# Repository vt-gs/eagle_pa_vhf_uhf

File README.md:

# eagle_pa_vhf_uhf
VHF/UHF Power Amplifier control board EagleCAD files

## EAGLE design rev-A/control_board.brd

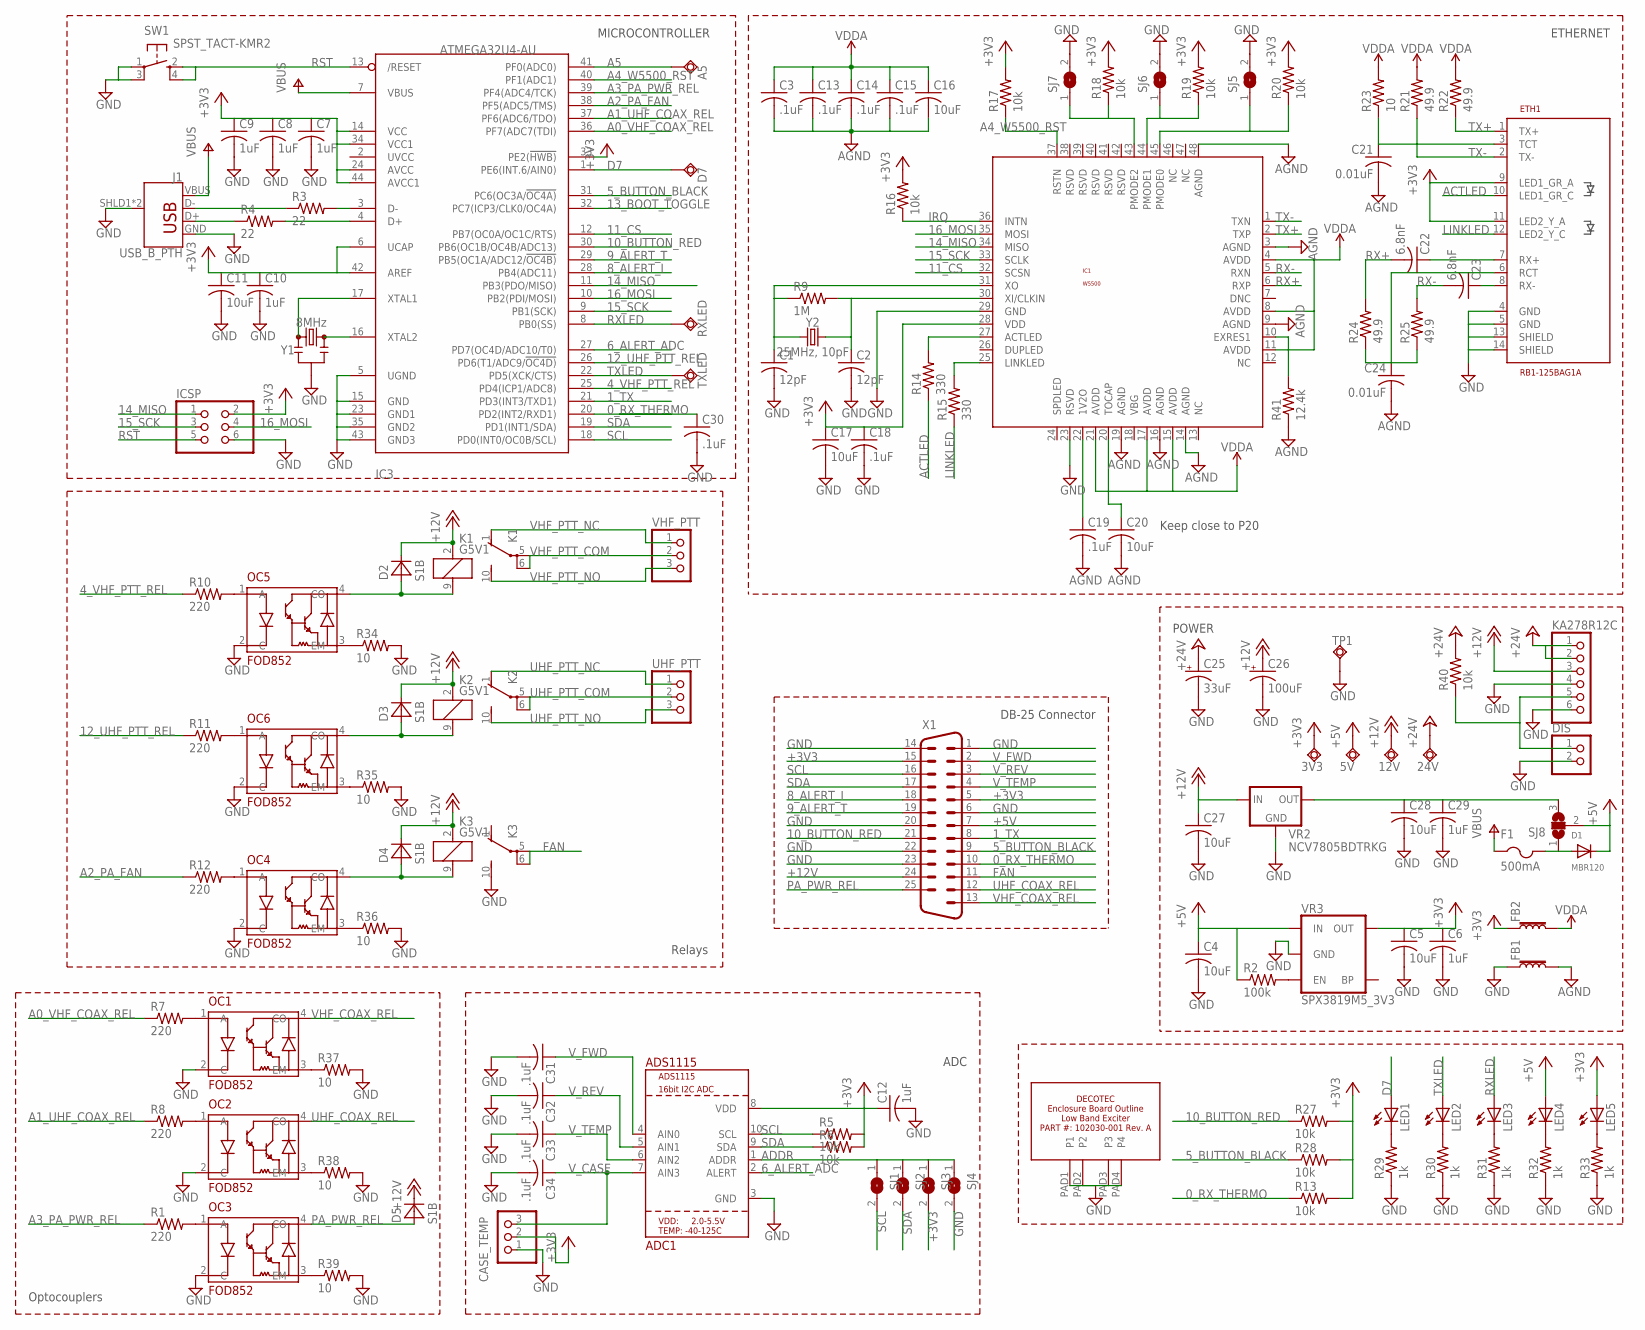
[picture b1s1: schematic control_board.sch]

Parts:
3V3, 5V, 12V, 24V: TPSQTP20SQ; TP20SQ
A5: TPSQTP20SQ; TP20SQ
ADC1: ADS1115; MSOP10
C1, C2: 12pF; C0805K
C3, C13, C14, C15, C18, C19, C30, C31, C32, C33, C34: .1uF; C0805K
C4, C5, C11, C16, C17, C20, C27, C28: 10uF; C0805K
C6, C7, C8, C9, C10, C12, C29: 1uF; C0805K
C21, C24: 0.01uF; C0805K
C22, C23: 6.8nF; C0805K
C25: 33uF; PANASONIC_C
C26: 100uF; PANASONIC_D
CASE_TEMP: PINHD-1X3; 1X03
D1: MBR120; SOD-123
D2, D3, D4, D5: S1B; DO214AC
D7: TPSQTP20SQ; TP20SQ
DIS: PINHD-1X2; 1X02
ETH1: RB1-125BAG1A
F1: 500mA; R1206
FB1, FB2: FERRITE_BEAD; 0805
IC1: W5500; LQFP48
IC3: ATMEGA32U4-AU; TQFP44
ICSP: PINHD-2X3; 2X03
J1: USB_B_PTH; USB-B-PTH
K1, K2, K3: G5V1
KA278R12C: PINHD-1X6; 1X06
LED1, LED2, LED3, LED4, LED5: LEDCHIPLED_0805; CHIPLED_0805
OC1, OC2, OC3, OC4, OC5, OC6: FOD852; SMD4-7
R1, R7, R8, R10, R11, R12: 220; R0805
R2: 100k; R0805
R3, R4: 22; R0805
R5, R6, R13, R16, R17, R18, R19, R20, R27, R28, R40: 10k; R0805
R9: 1M; R0805
R14, R15: 330; R0805
R21, R22, R24, R25: 49.9; R0805
R23, R34, R35, R36, R37, R38, R39: 10; R0805
R29, R30, R31, R32, R33: 1k; R0805
R41: 12.4k; R0805
RXLED: TPSQTP20SQ; TP20SQ
SJ1, SJ2, SJ3, SJ4, SJ5, SJ6, SJ7: SJ
SJ8: SJ2W; SJ_2
SW1: SPST_TACT-KMR2; KMR2
TP1: TPSQTP20SQ; TP20SQ
TXLED: TPSQTP20SQ; TP20SQ
U$3: DECOTEC_102030-001AV3; DECOTEC_102030-001A_V3
UHF_PTT: PINHD-1X3; 1X03
VHF_PTT: PINHD-1X3; 1X03
VR2: NCV7805BDTRKG; DPACK
VR3: SPX3819M5_3V3; SOT23-5
X1: DB25_MALEVB; M25VB
Y1: 8MHz; RESONATOR-SMD-3.2X1.3
Y2: 25MHz, 10pF; CRYSTAL-SMD-3.2X2.5MM

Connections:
0_RX_THERMO: C30.1, IC3.20 (PD2(INT2/RXD1)), R13.1, X1.10
1_TX: IC3.21 (PD3(INT3/TXD1)), X1.8
4_VHF_PTT_REL: IC3.25 (PD4(ICP1/ADC8)), R10.1
5_BUTTON_BLACK: IC3.31 (PC6(OC3A/!OC4A)), R28.1, X1.9
6_ALERT_ADC: ADC1.2 (ALERT), IC3.27 (PD7(OC4D/ADC10/T0))
8_ALERT_I: IC3.28 (PB4(ADC11)), X1.18
9_ALERT_T: IC3.29 (PB5(OC1A/ADC12/!OC4B)), X1.19
10_BUTTON_RED: IC3.30 (PB6(OC1B/OC4B/ADC13)), R27.1, X1.21
11_CS: IC1.32 (SCSN), IC3.12 (PB7(OC0A/OC1C/RTS))
12_UHF_PTT_REL: IC3.26 (PD6(T1/ADC9/!OC4D)), R11.1
13_BOOT_TOGGLE: IC3.32 (PC7(ICP3/CLK0/OC4A))
14_MISO: IC1.34 (MISO), IC3.11 (PB3(PDO/MISO)), ICSP.1
15_SCK: IC1.33 (SCLK), IC3.9 (PB1(SCK)), ICSP.3
16_MOSI: IC1.35 (MOSI), IC3.10 (PB2(PDI/MOSI)), ICSP.4
+3V3: 3V3.TP, ADC1.8 (VDD), C5.1, C6.1, C7.1, C8.1, C9.1, C10.1, C11.1, C12.1, C17.1, C18.1, CASE_TEMP.2, ETH1.9 (LED1_GR_A), ETH1.11 (LED2_Y_A), FB2.1, IC1.28 (VDD), IC3.6 (UCAP), IC3.14 (VCC), IC3.24 (AVCC), IC3.33 (PE2(!HWB)), IC3.34 (VCC1), IC3.42 (AREF), IC3.44 (AVCC1), ICSP.2, LED5.A, R5.2, R6.2, R13.2, R16.2, R17.2, R18.2, R19.2, R20.2, R27.2, R28.2, SJ3.2, VR3.5 (OUT), X1.5, X1.15
+5V: 5V.TP, C4.1, D1.C, LED4.A, R2.1, SJ8.2, VR3.1 (IN), X1.7
+12V: 12V.TP, C26.+, C27.1, D2.C, D3.C, D4.C, D5.C, K1.2 (1), K2.2 (1), K3.2 (1), KA278R12C.3, VR2.1 (IN), X1.24
+24V: 24V.TP, C25.+, KA278R12C.1, KA278R12C.2, R40.2
A0_VHF_COAX_REL: IC3.36 (PF7(ADC7(TDI)), R7.1
A1_UHF_COAX_REL: IC3.37 (PF6(ADC6/TDO)), R8.1
A2_PA_FAN: IC3.38 (PF5(ADC5/TMS)), R12.1
A3_PA_PWR_REL: IC3.39 (PF4(ADC4/TCK)), R1.1
A4_W5500_RST: IC1.37 (RSTN), IC3.40 (PF1(ADC1)), R17.1
A5: A5.TP, IC3.41 (PF0(ADC0))
ACTLED: ETH1.10 (LED1_GR_C), R14.1
ADDR: ADC1.1 (ADDR), SJ1.1, SJ2.1, SJ3.1, SJ4.1
AGND: C3.2, C13.2, C14.2, C15.2, C16.2, C19.2, C20.2, C21.2, C24.2, FB1.2, IC1.3 (AGND), IC1.9 (AGND), IC1.14 (AGND), IC1.16 (AGND), IC1.19 (AGND), IC1.48 (AGND), R41.1
D7: D7.TP, IC3.1 (PE6(INT.6/AIN0)), LED1.A
FAN: K3.5, K3.6, X1.11
GND: ADC1.3 (GND), C1.2, C2.2, C4.2, C5.2, C6.2, C7.2, C8.2, C9.2, C10.2, C11.2, C12.2, C17.2, C18.2, C25.-, C26.-, C27.2, C28.2, C29.2, C30.2, C31.2, C32.2, C33.2, C34.2, CASE_TEMP.1, DIS.2, ETH1.4 (GND), ETH1.5 (GND), ETH1.13 (SHIELD), ETH1.14 (SHIELD), FB1.1, IC1.23 (RSVD), IC1.29 (GND), IC3.5 (UGND), IC3.15 (GND), IC3.23 (GND1), IC3.35 (GND2), IC3.43 (GND3), ICSP.6, J1.GND, J1.SHLD1 (SHIELD), J1.SHLD2 (SHIELD), K3.10 (S), KA278R12C.4, KA278R12C.6, OC1.2 (C), OC2.2 (C), OC3.2 (C), OC4.2 (C), OC5.2 (C), OC6.2 (C), R29.1, R30.1, R31.1, R32.1, R33.1, R34.2, R35.2, R36.2, R37.2, R38.2, R39.2, SJ4.2, SJ5.2, SJ6.2, SJ7.2, SW1.1, SW1.3 (P1), TP1.TP, U$3.PAD1 (P1), U$3.PAD2 (P2), U$3.PAD3 (P3), U$3.PAD4 (P4), VR2.4 (GND), VR3.2 (GND), X1.1, X1.6, X1.14, X1.20, X1.22, X1.23, Y1.2
IRQ: IC1.36 (INTN), R16.1
LINKLED: ETH1.12 (LED2_Y_C), R15.1
unnamed: OC3.1 (A), R1.2
unnamed: D4.A, K3.9 (2), OC4.4 (CO)
unnamed: R2.2, VR3.3 (EN)
unnamed: IC3.17 (XTAL1), Y1.1
unnamed: IC3.16 (XTAL2), Y1.3
unnamed: C1.1, IC1.31 (XO), R9.1, Y2.1
unnamed: C2.1, IC1.30 (XI/CLKIN), R9.2, Y2.3 (2)
unnamed: J1.D-, R3.1
unnamed: IC3.3 (D-), R3.2
unnamed: IC3.4 (D+), R4.2
unnamed: J1.D+, R4.1
unnamed: OC1.1 (A), R7.2
unnamed: OC2.1 (A), R8.2
unnamed: OC5.1 (A), R10.2
unnamed: LED1.C, R29.2
unnamed: LED2.C, R30.2
unnamed: LED4.C, R32.2
unnamed: LED5.C, R33.2
unnamed: OC6.1 (A), R11.2
unnamed: OC4.1 (A), R12.2
unnamed: D2.A, K1.9 (2), OC5.4 (CO)
unnamed: D3.A, K2.9 (2), OC6.4 (CO)
unnamed: LED3.C, R31.2
unnamed: OC5.3 (EM), R34.1
unnamed: OC6.3 (EM), R35.1
unnamed: OC4.3 (EM), R36.1
unnamed: OC1.3 (EM), R37.1
unnamed: IC1.27 (ACTLED), R14.2
unnamed: IC1.25 (LINKLED), R15.2
unnamed: C28.1, C29.1, SJ8.3, VR2.3 (OUT)
unnamed: OC2.3 (EM), R38.1
unnamed: C20.1, IC1.20 (TOCAP)
unnamed: C19.1, IC1.22 (1V2O)
unnamed: C23.1, ETH1.8 (RX-)
unnamed: C22.1, ETH1.7 (RX+)
unnamed: C24.1, ETH1.6 (RCT), R24.1, R25.1
unnamed: D1.A, F1.2, SJ8.1
unnamed: OC3.3 (EM), R39.1
unnamed: DIS.1, KA278R12C.5, R40.1
unnamed: IC1.10 (EXRES1), R41.2
PA_PWR_REL: D5.A, OC3.4 (CO), X1.25
PMODE0: IC1.45 (PMODE0), R20.1, SJ5.1
PMODE1: IC1.44 (PMODE1), R19.1, SJ6.1
PMODE2: IC1.43 (PMODE2), R18.1, SJ7.1
RST: IC3.13 (/RESET), ICSP.5, SW1.2 (S), SW1.4 (S1)
RX+: C22.2, IC1.6 (RXP), R24.2
RX-: C23.2, IC1.5 (RXN), R25.2
RXLED: IC3.8 (PB0(SS)), LED3.A, RXLED.TP
SCL: ADC1.10 (SCL), IC3.18 (PD0(INT0/OC0B/SCL)), R5.1, SJ1.2, X1.16
SDA: ADC1.9 (SDA), IC3.19 (PD1(INT1/SDA)), R6.1, SJ2.2, X1.17
TCT: C21.1, ETH1.3 (TCT), R23.1
TX+: ETH1.1 (TX+), IC1.2 (TXP), R22.1
TX-: ETH1.2 (TX-), IC1.1 (TXN), R21.1
TXLED: IC3.22 (PD5(XCK/CTS)), LED2.A, TXLED.TP
UHF_COAX_REL: OC2.4 (CO), X1.12
UHF_PTT_COM: K2.5, K2.6, UHF_PTT.2
UHF_PTT_NC: K2.1 (O), UHF_PTT.1
UHF_PTT_NO: K2.10 (S), UHF_PTT.3
VBUS: F1.1, IC3.7 (VBUS), J1.VBUS
VDDA: C3.1, C13.1, C14.1, C15.1, C16.1, FB2.2, IC1.4 (AVDD), IC1.8 (AVDD), IC1.11 (AVDD), IC1.15 (AVDD), IC1.17 (AVDD), IC1.21 (AVDD), R21.2, R22.2, R23.2
VHF_COAX_REL: OC1.4 (CO), X1.13
VHF_PTT_COM: K1.5, K1.6, VHF_PTT.2
VHF_PTT_NC: K1.1 (O), VHF_PTT.1
VHF_PTT_NO: K1.10 (S), VHF_PTT.3
V_CASE: ADC1.7 (AIN3), C34.1, CASE_TEMP.3
V_FWD: ADC1.4 (AIN0), C31.1, X1.2
V_REV: ADC1.5 (AIN1), C32.1, X1.3
V_TEMP: ADC1.6 (AIN2), C33.1, X1.4

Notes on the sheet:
Keep close to P20
ETHERNET
MICROCONTROLLER
Optocouplers
DB-25 Connector
Relays
ADC
POWER

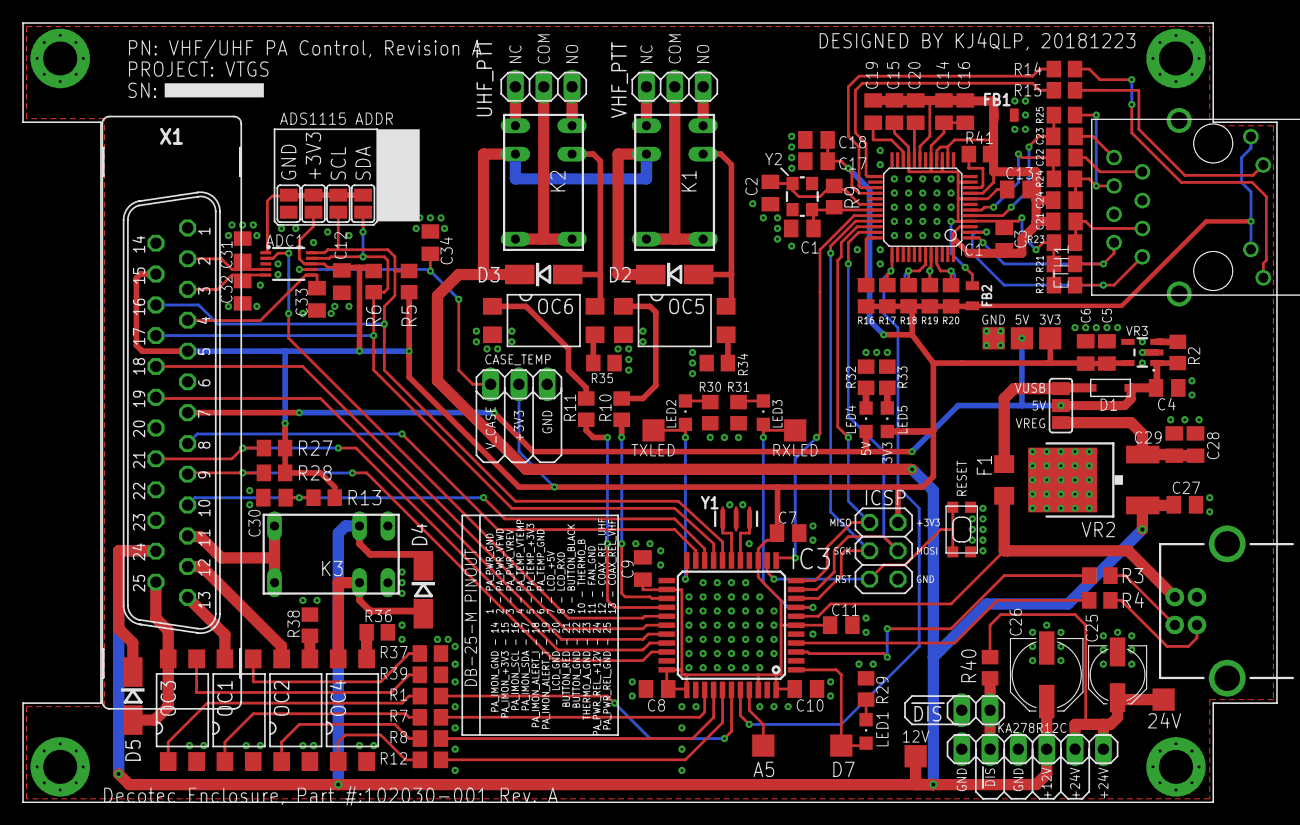
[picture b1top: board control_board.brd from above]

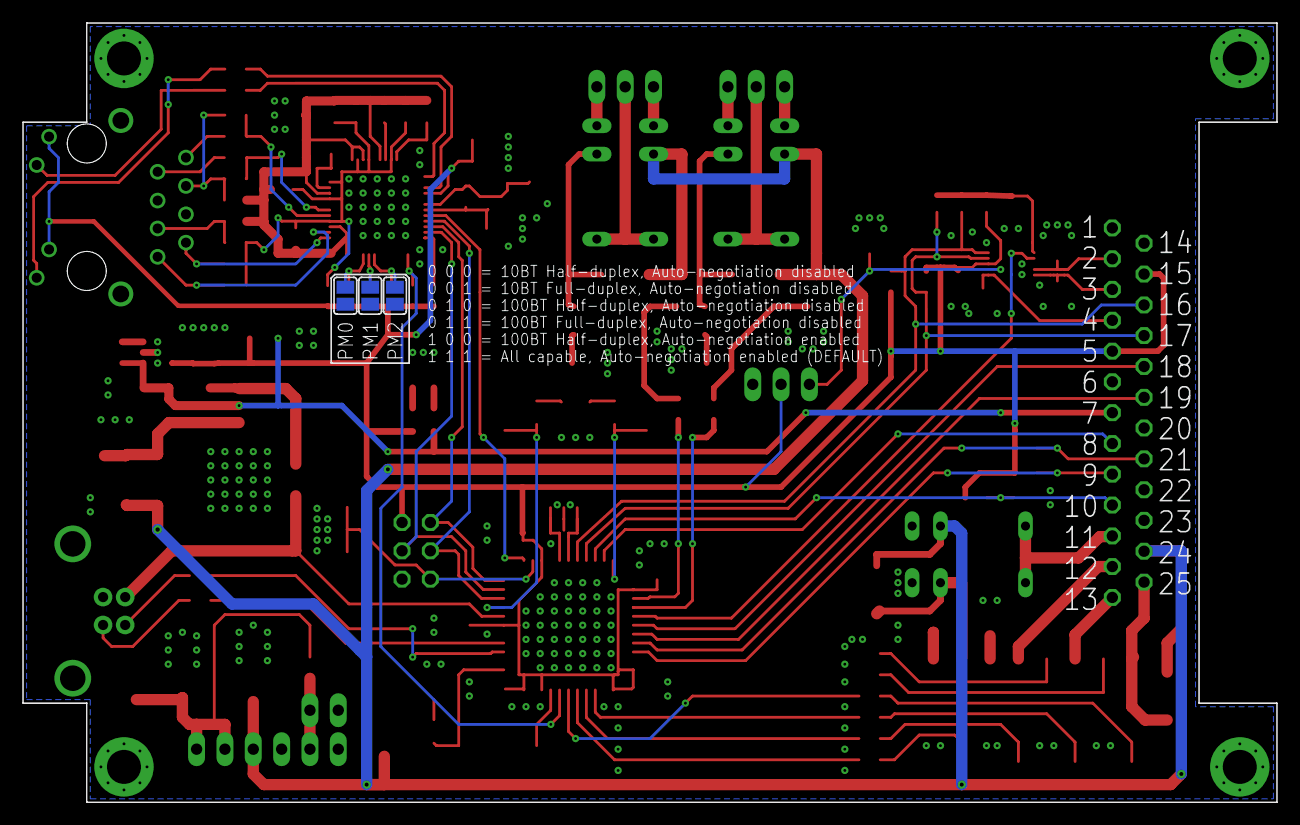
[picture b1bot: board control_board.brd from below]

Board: 2 copper layers, 112.4 x 69.8 mm, 131 parts (3 on the bottom side), 99 nets.

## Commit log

2018-07-03 moving VHF/UHF control board eagle files from original huge 'eagle' repo to its own stand alone repo.
2018-07-03 updated eagle DESCRIPTION file
2018-12-23 adding revision A.....multiple fixes.
2018-12-23 adding gitignore
2018-12-24 lots of updates, added caps for ADC, swapped out 5v vreg, moved a lot of parts around, added flyback diodes to relays.
2018-12-24 added to silkscreen, added osh park top/bottom pngs. This version ordered.
2019-01-04 fixed R41 value to 12.4k

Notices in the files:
parts and their libraries:
SparkFun-Connectors: Licensing: Creative Commons ShareAlike 4.0 International - https://creativecommons.org/licenses/by-sa/4.0
